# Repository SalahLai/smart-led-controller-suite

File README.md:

# Smart LED Controller Suite — Full-Stack IoT Lighting System

> Production-grade ambient lighting ecosystem comprising a custom KiCad hardware PCB, ESP32 PWM firmware, and an Electron + React desktop controller application.

---

## Overview

The **Smart LED Controller Suite** is a full-stack IoT ambient lighting solution built from schematic to user interface.

The system controls multi-channel 12V/5V RGB LED strips through high-frequency PWM switching. Users adjust color palettes, brightness curves, and automated lighting profiles via a desktop Electron application communicating with an onboard ESP32 controller.

---

## Features

- **Custom KiCad PCB**: High-current MOSFET switching stages designed in KiCad 10, complete with schematic, 3D footprint clearances, and thermal relief ground planes.
- **Smooth 8-Bit Hardware PWM**: ESP32 `ledc` peripheral operating at 5 kHz eliminates visual flickering across all dimming ranges.
- **Cross-Platform Electron Desktop App**: Modern desktop GUI built with React 18, color pickers, and automated serial connection management.
- **Full-Stack Architecture**: Demonstrates complete end-to-end integration across PCB hardware design, embedded microcontroller C++, and desktop frontend engineering.

---

## Hardware Specifications

| Parameter | Specification |
|---|---|
| **MCU** | ESP32 NodeMCU-32S (Xtensa LX6) |
| **Output Channels** | 3x High-Current PWM Channels (R: `GPIO 25`, G: `GPIO 26`, B: `GPIO 27`) |
| **PWM Frequency** | 5 kHz (8-bit resolution, 256 duty steps per channel) |
| **Operating Voltage** | 5V Logic, 12V LED Load Rail |
| **PCB Tool** | KiCad 10.0 (`LED_Controller.kicad_pro`) |

---

## System Architecture

```mermaid
graph LR
    subgraph Control_Layer [Electron and React Desktop App]
        A[Color Picker and Sliders] -->|Serial UART / Web Protocol| B[Command Dispatcher]
    end

    subgraph Hardware_Layer [ESP32 Controller and PCB]
        B --> C[ESP32 LEDC PWM Driver]
        C -->|5 kHz Hardware PWM| D[MOSFET Switching Stage]
        D -->|High-Current 12V Load| E[RGB LED Light Strips]
    end
```

---

## Project Structure

```text
smart-led-controller-suite/
├── hardware/                        # KiCad 10 Hardware Design
│   ├── LED_Controller.kicad_pro     # Project configuration
│   ├── LED_Controller.kicad_sch     # Schematic (MOSFET drivers, power filtering)
│   └── LED_Controller.kicad_pcb     # 2-layer PCB layout with copper ground planes
├── firmware/                        # ESP32 Embedded Firmware (PlatformIO)
│   ├── src/main.cpp                 # LEDC PWM hardware driver
│   └── platformio.ini
├── desktop_app/                     # Electron + React Desktop Application
│   ├── public/electron.js           # Electron main process & IPC bridges
│   ├── src/                         # React UI, color wheel, preset manager
│   ├── package.json
│   └── package-lock.json
└── README.md
```

---

## Getting Started

### 1. Flashing the Firmware

```bash
cd firmware
pio run --target upload
```

### 2. Running the Desktop Controller

Requirements: [Node.js](https://nodejs.org/) (v18+ recommended).

```bash
cd ../desktop_app
npm install
npm start
```

---

## Author

**Salah Lai**
- GitHub: [@SalahLai](https://github.com/SalahLai)
- Email: salah.lai.icloud@gmail.com

---

## License

This project is open-source and licensed under the [MIT License](LICENSE).

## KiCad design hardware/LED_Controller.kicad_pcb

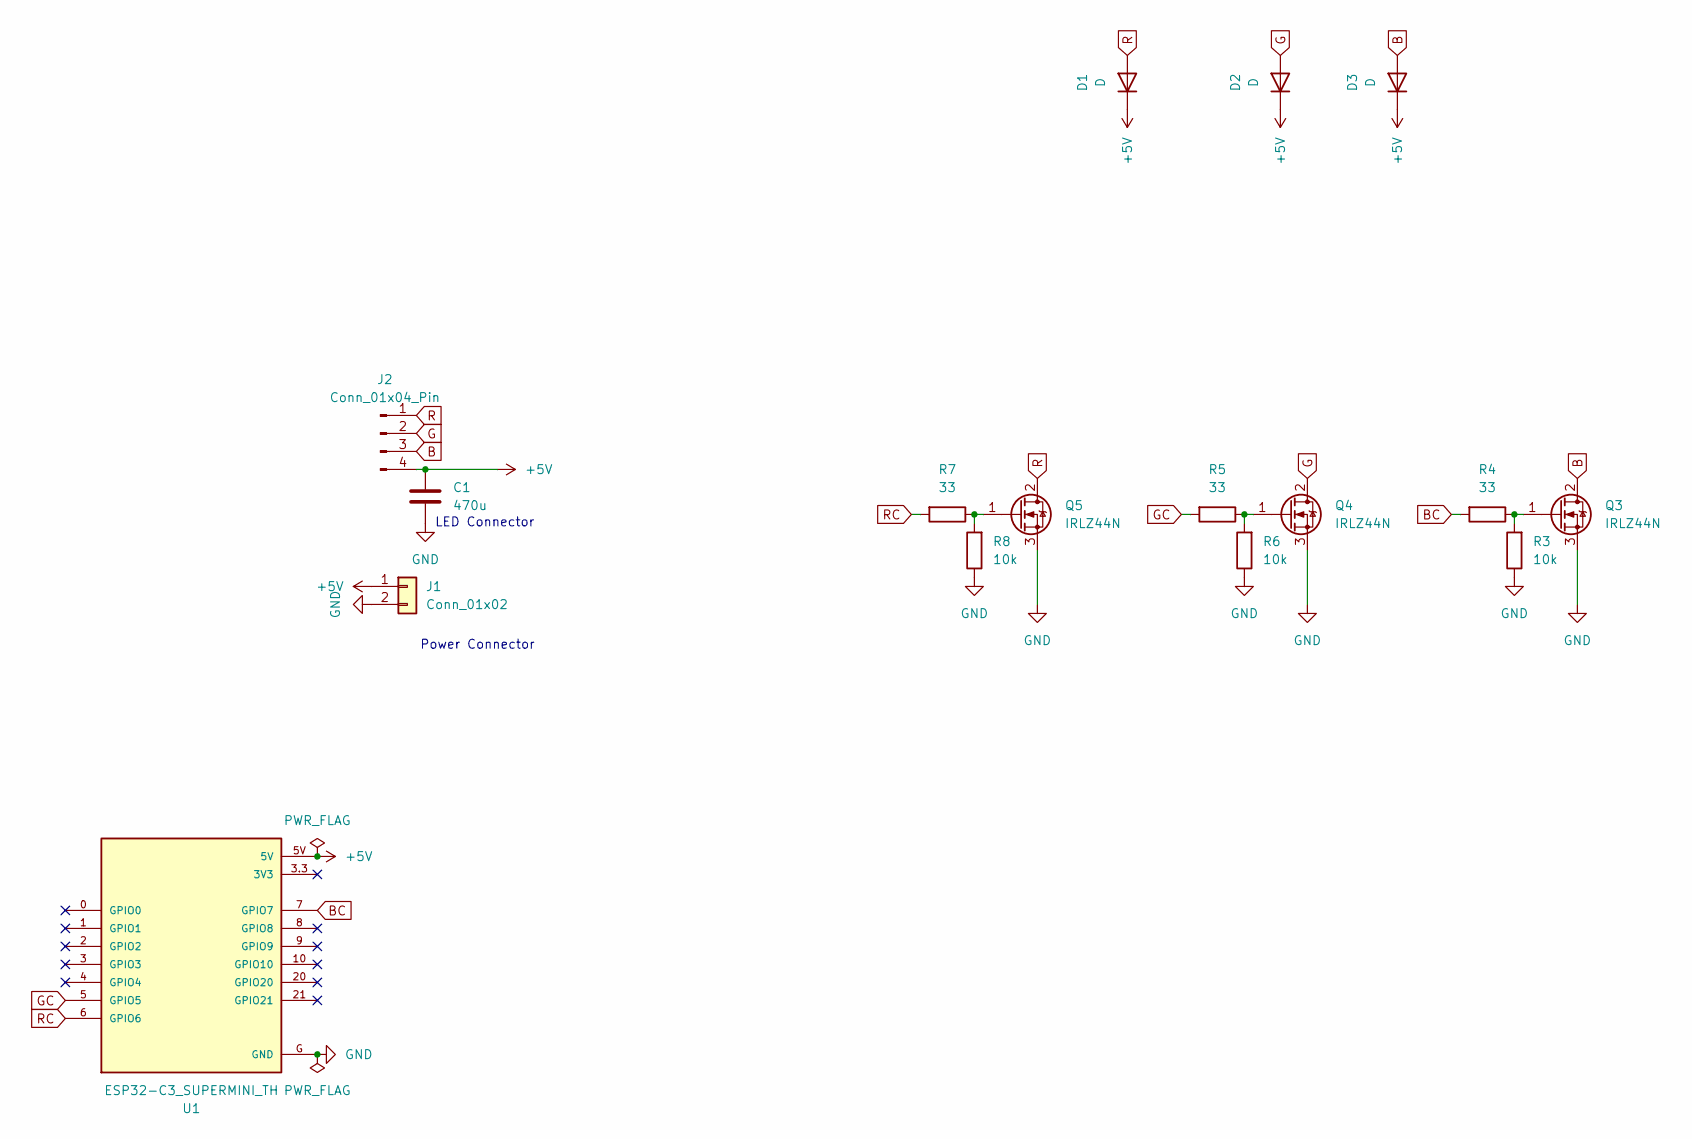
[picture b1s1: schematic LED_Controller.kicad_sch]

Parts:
C1: 470u; CP_Radial_D5.0mm_P2.50mm
D1, D2, D3: D; D_DO-41_SOD81_P10.16mm_Horizontal
J1: Conn_01x02; TerminalBlock_bornier-2_P5.08mm
J2: Conn_01x04_Pin; JST_XH_B4B-XH-A_1x04_P2.50mm_Vertical
Q3, Q4, Q5: IRLZ44N; TO-220-3_Horizontal_TabDown
R3, R6, R8: 10k; R_Axial_DIN0207_L6.3mm_D2.5mm_P7.62mm_Horizontal
R4, R5, R7: 33; R_Axial_DIN0207_L6.3mm_D2.5mm_P7.62mm_Horizontal
U1: ESP32-C3_SUPERMINI_TH; MODULE_ESP32-C3_SUPERMINI_TH

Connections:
+5V: C1.1, D1.1 (K), D2.1 (K), D3.1 (K), J1.1, J2.4, U1.5V
B: D3.2 (A), J2.3, Q3.2 (D)
BC: R4.2, U1.7 (GPIO7)
G: D2.2 (A), J2.2, Q4.2 (D)
GC: R5.2, U1.5 (GPIO5)
GND: C1.2, J1.2, Q3.3 (S), Q4.3 (S), Q5.3 (S), R3.1, R6.1, R8.1, U1.G (GND)
unnamed: Q3.1 (G), R3.2, R4.1
unnamed: Q4.1 (G), R5.1, R6.2
unnamed: Q5.1 (G), R7.1, R8.2
R: D1.2 (A), J2.1, Q5.2 (D)
RC: R7.2, U1.6 (GPIO6)

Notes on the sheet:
LED Connector
Power Connector

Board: 2 copper layers, 16 parts (0 on the bottom side), 11 nets, no tracks yet.
